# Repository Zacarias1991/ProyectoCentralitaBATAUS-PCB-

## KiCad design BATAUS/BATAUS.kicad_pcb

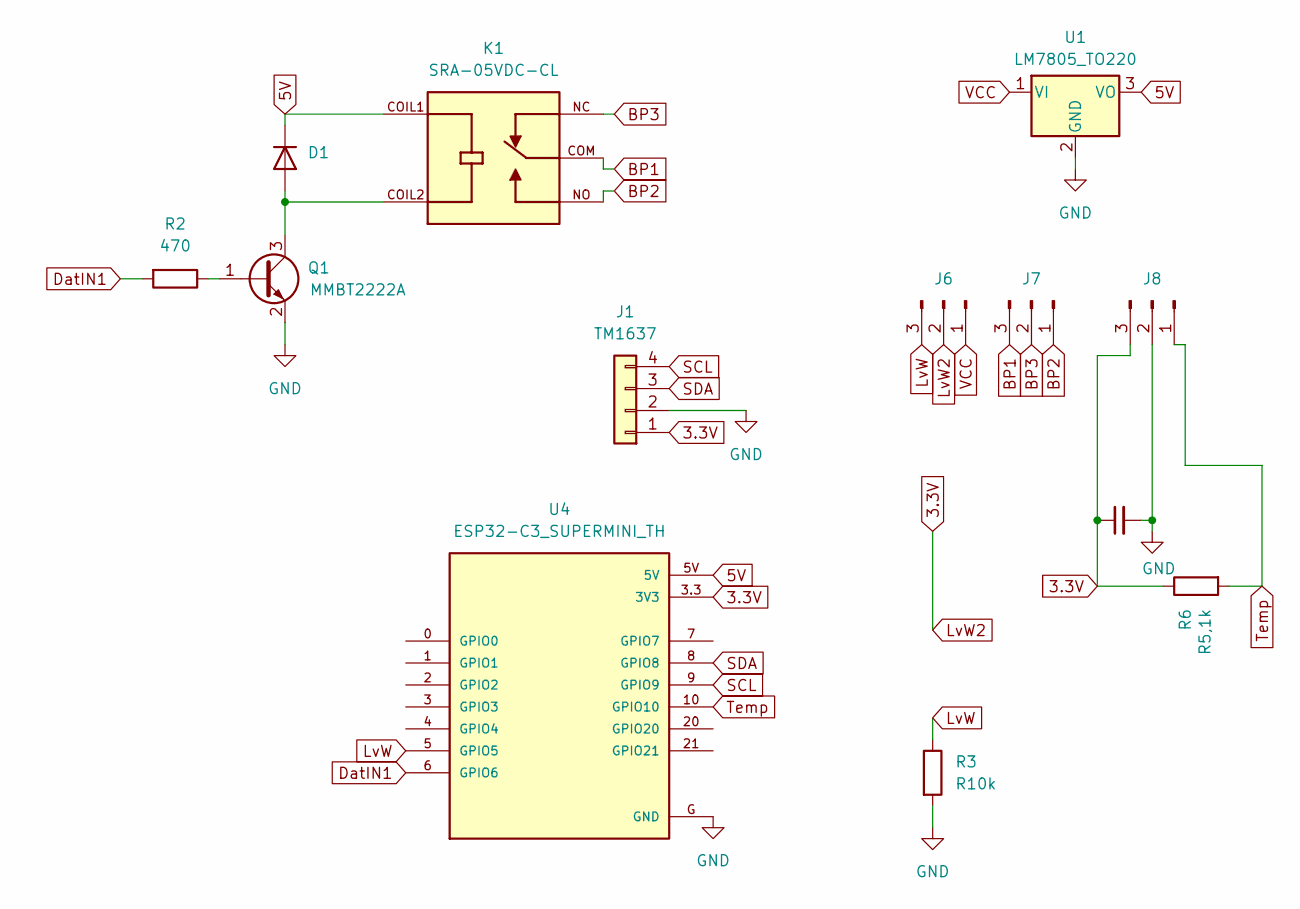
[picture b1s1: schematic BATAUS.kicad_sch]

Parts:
C1: C_Small; CP_Radial_Tantal_D5.0mm_P2.50mm
D1: D_SMA
J1: TM1637; PinHeader_1x04_P2.54mm_Vertical
J6, J8: TerminalBlock_Xinya_XY308-2.54-3P_1x03_P2.54mm_Horizontal
J7: TerminalBlock_4Ucon_1x03_P3.50mm_Vertical
K1: SRA-05VDC-CL; RELAY_SRA-05VDC-CL; PARTREV NA
Q1: MMBT2222A; SOT-23
R2: 470; R_Axial_DIN0207_L6.3mm_D2.5mm_P10.16mm_Horizontal
R3: R10k; R_Axial_DIN0207_L6.3mm_D2.5mm_P10.16mm_Horizontal
R6: R5,1k; R_Axial_DIN0207_L6.3mm_D2.5mm_P10.16mm_Horizontal
U1: LM7805_TO220; TO-220-3_Vertical
U4: ESP32-C3_SUPERMINI_TH; MODULE_ESP32-C3_SUPERMINI_TH

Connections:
3.3V: C1.1, J1.1, J6.2, J8.3, R6.1, U4.3.3 (3V3)
5V: D1.1 (K), K1.COIL1, U1.3 (VO), U4.5V
BP1: J7.3, K1.COM
BP2: J7.1, K1.NO
BP3: J7.2, K1.NC
DatIN1: R2.2, U4.6 (GPIO6)
GND: C1.2, J1.2, J8.2, Q1.2 (E), R3.2, U1.2 (GND), U4.G (GND)
LvW: J6.3, R3.1, U4.5 (GPIO5)
unnamed: D1.2 (A), K1.COIL2, Q1.3 (C)
unnamed: Q1.1 (B), R2.1
SCL: J1.4, U4.9 (GPIO9)
SDA: J1.3, U4.8 (GPIO8)
Temp: J8.1, R6.2, U4.10 (GPIO10)
VCC: J6.1, U1.1 (VI)

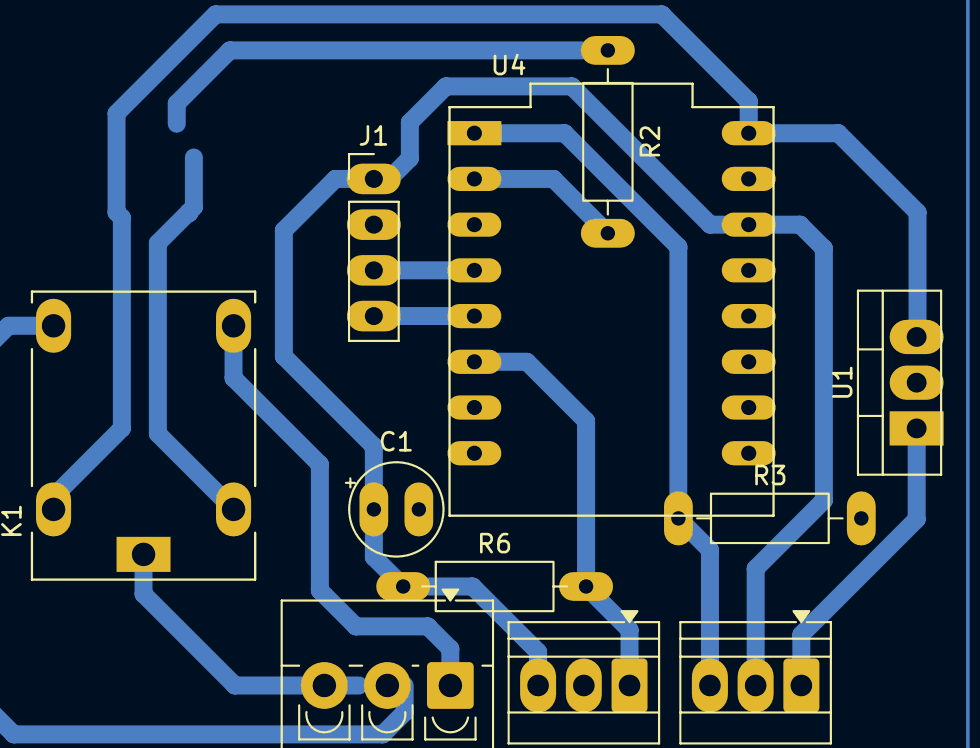
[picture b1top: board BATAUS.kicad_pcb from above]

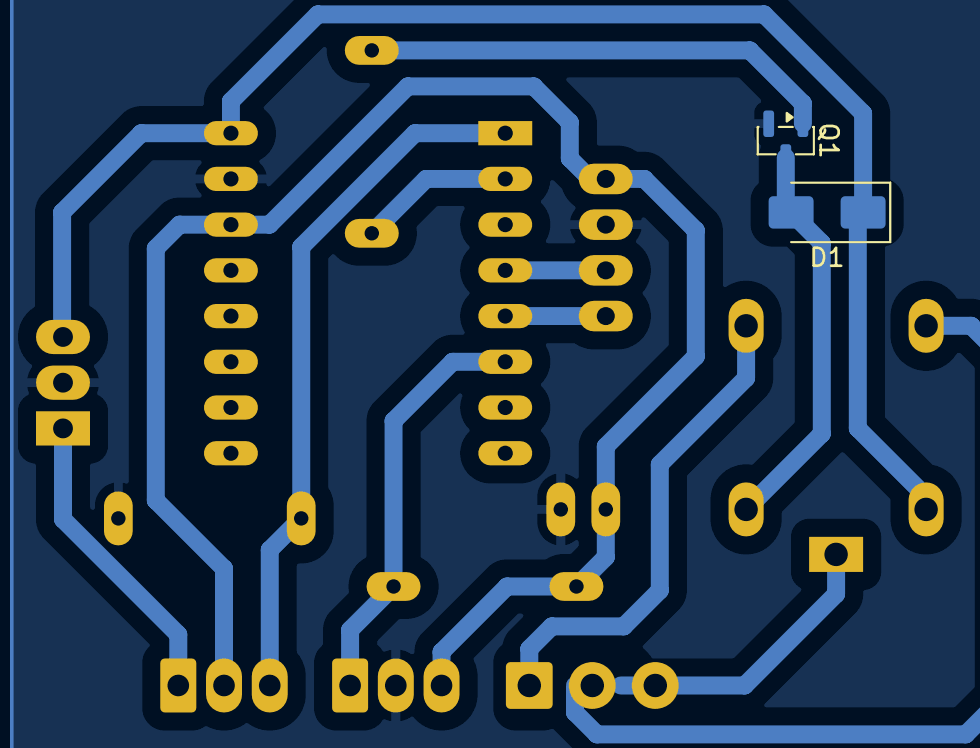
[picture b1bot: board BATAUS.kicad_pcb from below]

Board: 2 copper layers, 13 parts (2 on the bottom side), 14 nets.
